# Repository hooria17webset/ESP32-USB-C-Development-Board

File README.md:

ESP32 USB-C Development Board

A compact, custom-designed ESP32 development board featuring a USB-C port for power delivery and programming. Built for makers, hobbyists, and engineers working on IoT, wireless, and embedded applications.
Features

- Microcontroller:** ESP32 (dual-core Xtensa LX6, up to 240 MHz)
- Connectivity:** Wi-Fi 802.11 b/g/n + Bluetooth 4.2 / BLE
- USB Interface:** USB-C port for power and serial programming
- Flash Memory:** 4MB (expandable depending on variant)
- GPIO: Multiple digital I/O, ADC, DAC, SPI, I2C, UART, PWM
- Power Supply:5V via USB-C or external 3.3V regulated input
- Onboard LED:Status indicator
- Reset & Boot Buttons:For easy flashing and debugging
- Compact Form Factor:Breadboard-friendly pinout

Board Pinout
Requirements

- [Arduino IDE](https://www.arduino.cc/en/software) or [PlatformIO](https://platformio.org/)
- ESP32 board support package
- USB-C cable (data-capable)
- CP2102 / CH340 driver (if needed by your OS)

Installing ESP32 Board Support (Arduino IDE)

1. Open Arduino IDE → **File > Preferences**
2. Add this URL to "Additional Board Manager URLs":
   ```
   https://raw.githubusercontent.com/espressif/arduino-esp32/gh-pages/package_esp32_index.json
   ```
3. Go to **Tools > Board > Board Manager**, search `esp32`, and install.

1. Connect the board via USB-C.
2. Select the correct **COM port** under **Tools > Port**.
3. Choose board: **ESP32 Dev Module**.
4. Upload your sketch — hold the **BOOT** button if needed during upload.

Schematic & PCB Files

> The design files are available in the `/hardware` folder.

| File | Description |
|------|-------------|
| `schematic.pdf` | Full circuit schematic |
| `pcb.kicad_pcb` | KiCad PCB layout |
| `gerbers/` | Gerber files for fabrication |
| `bom.csv` | Bill of Materials |
 Specifications

| Parameter | Value |
|-----------|-------|
| MCU | ESP32-WROOM-32 |
| CPU Speed | Up to 240 MHz |
| Flash | 4 MB |
| SRAM | 520 KB |
| Operating Voltage | 3.3V |
| Input Voltage | 5V (USB-C) |
| USB Chip | CP2102 / CH340 |
| Dimensions | ~55mm x 28mm (approx.) |
 Power

The board is powered via the **USB-C port (5V)**. An onboard **AMS1117-3.3V LDO regulator** steps down to 3.3V for the ESP32. Ensure your USB-C cable supports data transfer for programming.

## Programming Modes

| Mode | How to Enter |
|------|-------------|
| Normal Boot | Press **RESET** |
| Flash Mode | Hold **BOOT**, press **RESET**, release **BOOT** |

 Known Issues / Notes

- Some USB-C cables are charge-only — use a data-capable cable for programming.
- The onboard LDO may get warm under heavy load; keep current draw under 500mA.
- If the board isn't detected, install the appropriate USB-to-Serial driver for your OS.
 License

This project is open-source under the [MIT License](LICENSE).

## Contributing

Pull requests are welcome! If you find a bug or want to improve the design, feel free to open an issue or submit a PR.

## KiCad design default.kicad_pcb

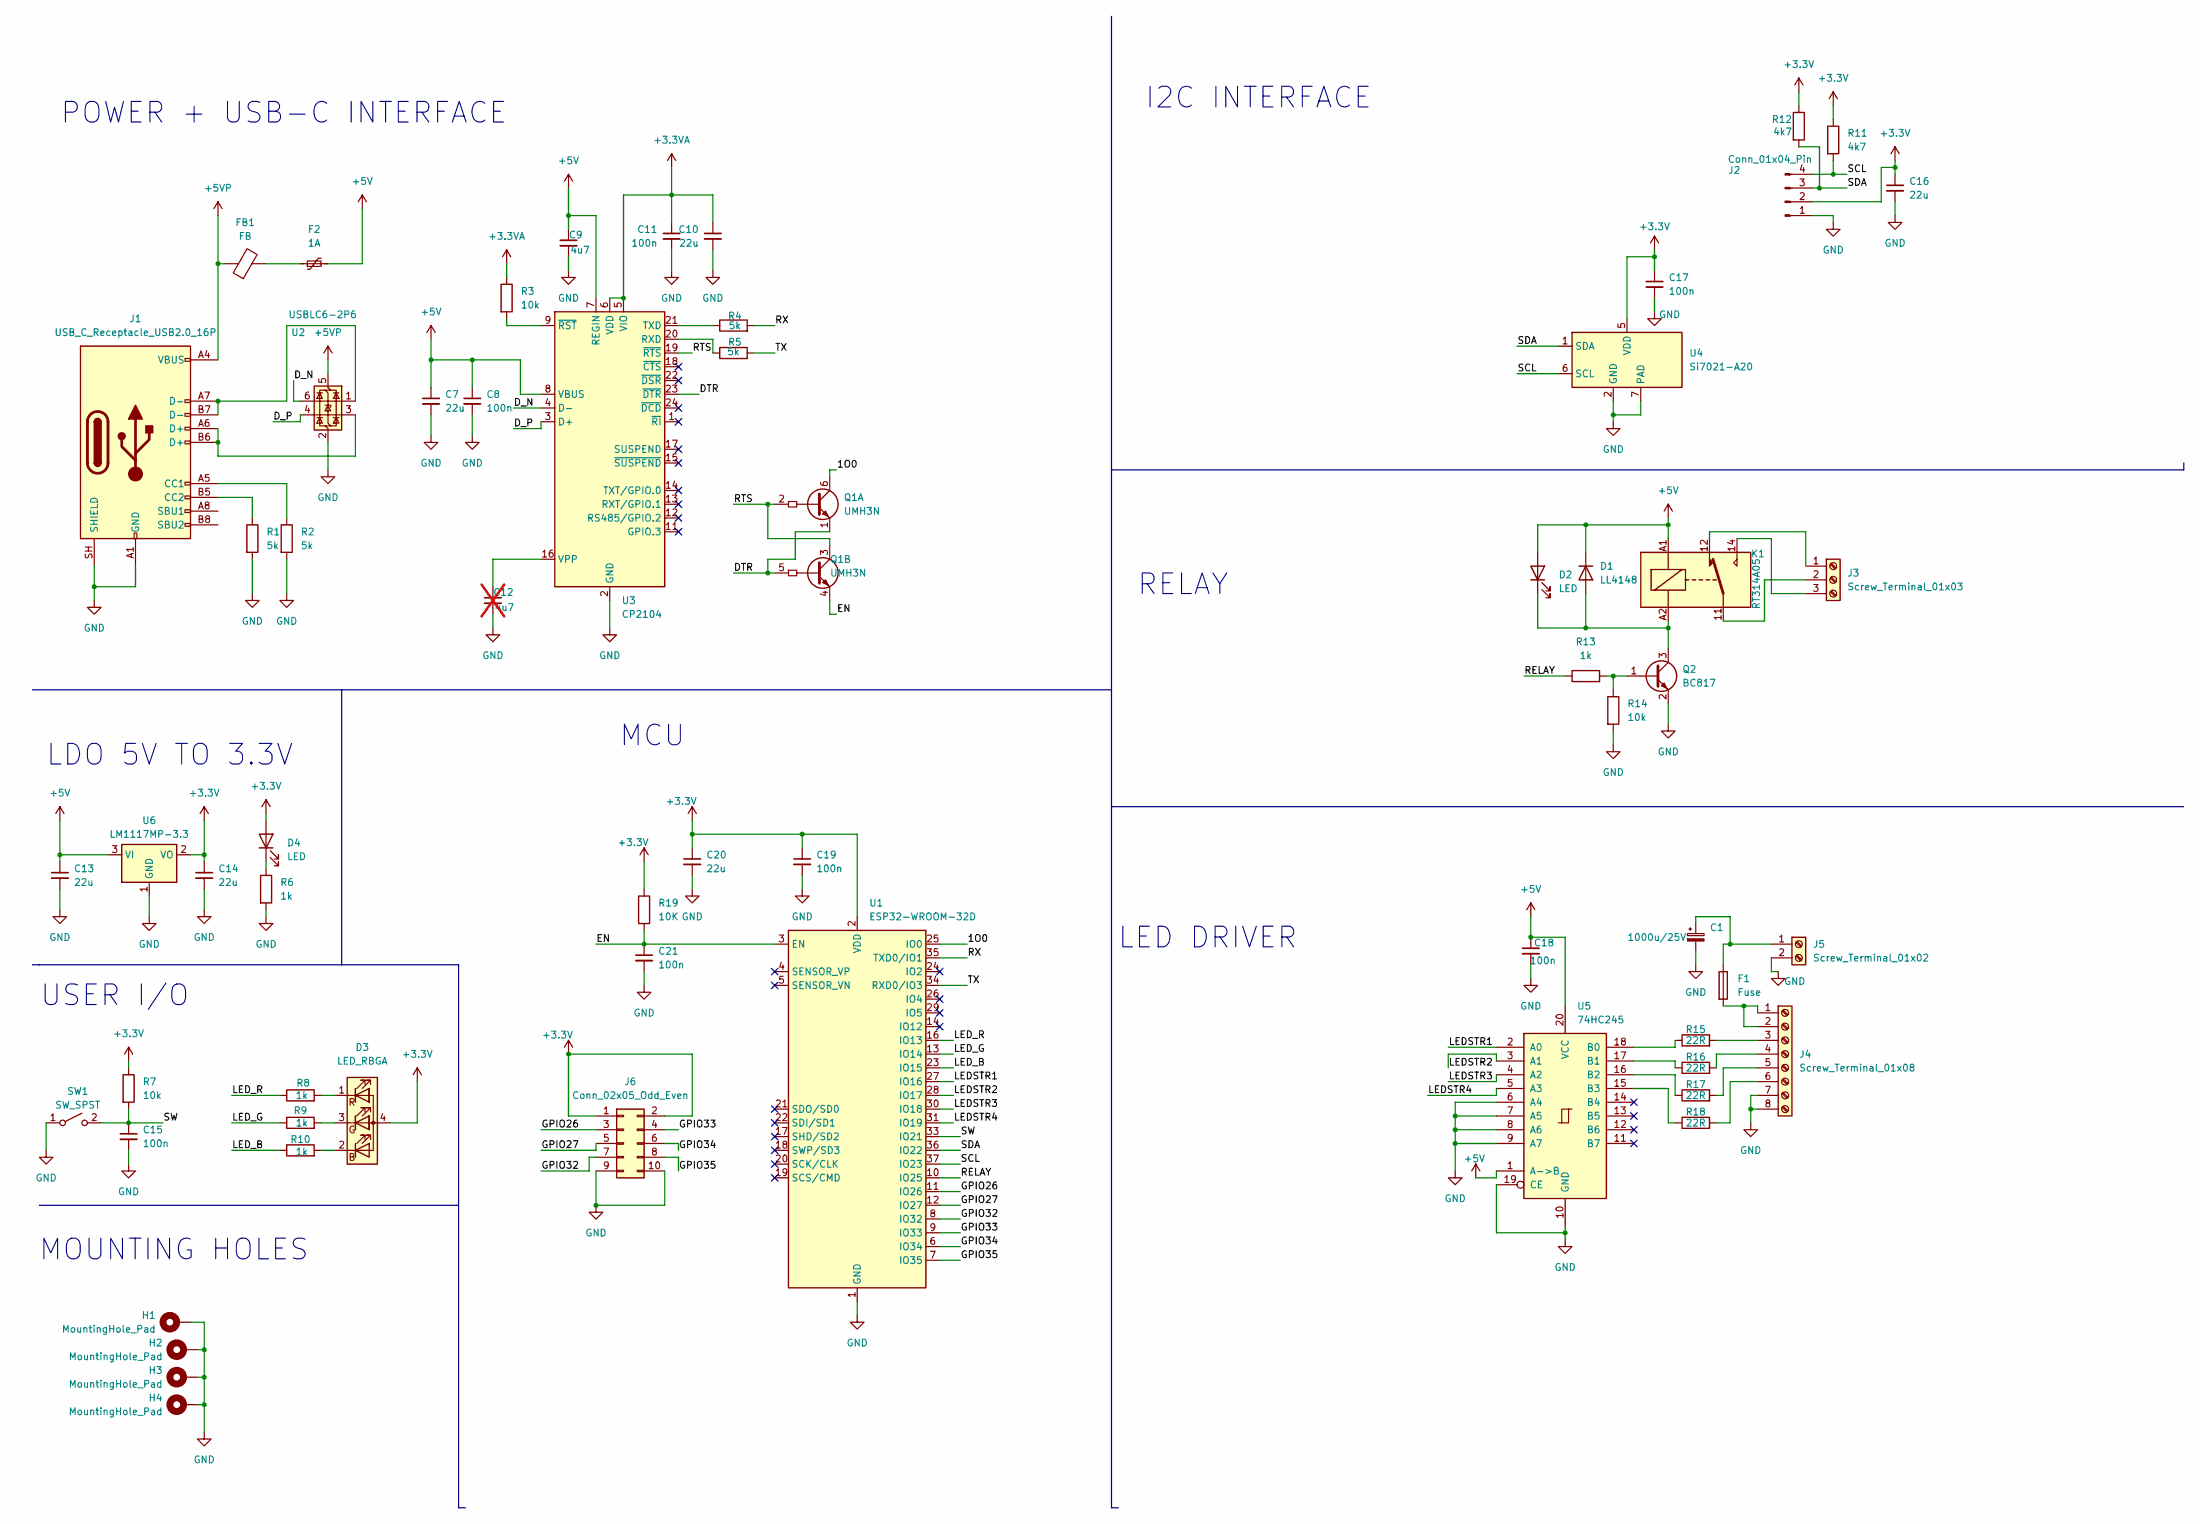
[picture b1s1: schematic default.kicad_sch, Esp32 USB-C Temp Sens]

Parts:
C1: 1000u/25V; CP_Radial_D10.0mm_P5.00mm
C7, C10, C13, C14, C16, C20: 22u; C_0805_2012Metric
C8, C11, C15, C17, C18, C19, C21: 100n; C_0402_1005Metric
C9: 4u7; C_0603_1608Metric
C12: 4u7; C_0603_1608Metric; not fitted
D1: LL4148; D_MiniMELF
D2, D4: LED; LED_0603_1608Metric
D3: LED_RBGA; LED_RGB_Wuerth-PLCC4_3.2x2.8mm_150141M173100
F1: Fuse; Fuse_1206_3216Metric
F2: 1A; Fuse_2920_7451Metric
FB1: FB; L_0603_1608Metric
H1, H2, H3, H4: MountingHole_Pad; MountingHole_3.2mm_M3_Pad_Via
J1: USB_C_Receptacle_USB2.0_16P; USB_C_Receptacle_HRO_TYPE-C-31-M-12
J2: Conn_01x04_Pin; PinHeader_1x04_P2.54mm_Horizontal
J3: Screw_Terminal_01x03; TerminalBlock_Phoenix_MKDS-1,5-3-5.08_1x03_P5.08mm_Horizont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
J4: Screw_Terminal_01x08; TerminalBlock_Phoenix_MKDS-1,5-8-5.08_1x08_P5.08mm_Horizont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
J5: Screw_Terminal_01x02; TerminalBlock_Phoenix_MKDS-1,5-2-5.08_1x02_P5.08mm_Horizont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
J6: Conn_02x05_Odd_Even; PinHeader_2x05_P2.54mm_Vertical
K1: RT314A05; Relay_SPDT_Schrack-RT1-16A-FormC_RM5mm
Q1: UMH3N; SOT-363_SC-70-6
Q2: BC817; SOT-23
R1, R2, R4, R5: 5k; R_0402_1005Metric
R3, R7, R14: 10k; R_0402_1005Metric
R6, R8, R9, R10, R13: 1k; R_0402_1005Metric
R11, R12: 4k7; R_0402_1005Metric
R15, R16, R17, R18: 22R; R_0402_1005Metric
R19: 10K; R_0402_1005Metric
SW1: SW_SPST; SW_Push_1P1T_NO_CK_PTS125Sx85PSMTR
U1: ESP32-WROOM-32D
U2: USBLC6-2P6; SOT-666
U3: CP2104; QFN-24-1EP_4x4mm_P0.5mm_EP2.6x2.6mm
U4: Si7021-A20; DFN-6-1EP_3x3mm_P1mm_EP1.5x2.4mm
U5: 74HC245; DIP-20_W7.62mm
U6: LM1117MP-3.3; SOT-223-3_TabPin2

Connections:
+3.3V: C14.1, C16.1, C17.1, C19.1, C20.1, D3.4 (A), D4.2 (A), J2.2, J6.1, J6.2, R7.1, R11.1, R12.1, R19.1, U1.2 (VDD), U4.5 (VDD), U6.2 (VO)
+3.3VA: C10.1, C11.1, R3.1, U3.5 (VIO), U3.6 (VDD)
+5V: C7.1, C8.1, C9.1, C13.1, C18.1, D1.1 (K), D2.2 (A), F2.2, K1.A1, U3.7 (REGIN), U3.8 (VBUS), U5.1 (A->B), U5.20 (VCC), U6.3 (VI)
+5VP: FB1.1, J1.A4 (VBUS), J1.A9 (VBUS), J1.B4 (VBUS), J1.B9 (VBUS), U2.5 (VBUS)
/1O0: Q1.6 (C1), U1.25 (IO0)
/DTR: Q1.1 (E1), Q1.5 (B2), U3.23 (~DTR)
/D_N: U2.6 (I/O1), U3.4 (D-)
/D_P: U2.4 (I/O2), U3.3 (D+)
/EN: C21.1, Q1.4 (E2), R19.2, U1.3 (EN)
/GPIO26: J6.3, U1.11 (IO26)
/GPIO27: J6.5, U1.12 (IO27)
/GPIO32: J6.7, U1.8 (IO32)
/GPIO33: J6.4, U1.9 (IO33)
/GPIO34: J6.6, U1.6 (IO34)
/GPIO35: J6.8, U1.7 (IO35)
/LEDSTR1: U1.27 (IO16), U5.2 (A0)
/LEDSTR2: U1.28 (IO17), U5.3 (A1)
/LEDSTR3: U1.30 (IO18), U5.4 (A2)
/LEDSTR4: U1.31 (IO19), U5.5 (A3)
/LED_B: R10.1, U1.23 (IO15)
/LED_G: R9.1, U1.13 (IO14)
/LED_R: R8.1, U1.16 (IO13)
/RELAY: R13.1, U1.10 (IO25)
/RTS: Q1.2 (B1), Q1.3 (C2), U3.19 (~RTS)
/RX: R4.2, U1.35 (TXD0/IO1)
/SCL: J2.4, R11.2, U1.37 (IO23), U4.6 (SCL)
/SDA: J2.3, R12.2, U1.36 (IO22), U4.1 (SDA)
/SW: C15.1, R7.2, SW1.2 (B), U1.33 (IO21)
/TX: R5.2, U1.34 (RXD0/IO3)
GND: C1.2, C7.2, C8.2, C9.2, C10.2, C11.2, C12.2, C13.2, C14.2, C15.2, C16.2, C17.2, C18.2, C19.2, C20.2, C21.2, H1.1 (1_1), H2.1 (1_1), H3.1 (1_1), H4.1 (1_1), J1.A1 (GND), J1.A12 (GND), J1.B1 (GND), J1.B12 (GND), J1.SH (SHIELD), J2.1, J4.7, J4.8, J5.2, J6.9, J6.10, Q2.2 (E), R1.2, R2.2, R6.2, R14.2, SW1.1 (A), U1.1 (GND), U1.15 (GND), U1.38 (GND), U1.39 (GND), U2.2 (GND), U3.2 (GND), U3.25 (GND), U4.2 (GND), U4.7 (PAD), U5.6 (A4), U5.7 (A5), U5.8 (A6), U5.9 (A7), U5.10 (GND), U5.19 (CE), U6.1 (GND)
unnamed: D1.2 (A), D2.1 (K), K1.A2, Q2.3 (C)
unnamed: D3.2 (BK), R10.2
unnamed: D3.3 (GK), R9.2
unnamed: D3.1 (RK), R8.2
unnamed: D4.1 (K), R6.1
unnamed: F2.1, FB1.2
unnamed: J1.A5 (CC1), R2.1
unnamed: J1.B5 (CC2), R1.1
unnamed: J1.A6 (D+), J1.B6 (D+), U2.3 (I/O2)
unnamed: J1.A7 (D-), J1.B7 (D-), U2.1 (I/O1)
unnamed: J3.1, K1.12
unnamed: J3.2, K1.11
unnamed: J3.3, K1.14
unnamed: F1.2, J4.1, J4.2
unnamed: J4.3, R15.2
unnamed: J4.4, R16.2
unnamed: J4.5, R17.2
unnamed: J4.6, R18.2
unnamed: C1.1, F1.1, J5.1
unnamed: Q2.1 (B), R13.2, R14.1
unnamed: R5.1, U3.20 (RXD)
unnamed: R4.1, U3.21 (TXD)
unnamed: C12.1, U3.16 (VPP)
unnamed: R3.2, U3.9 (~RST)
unnamed: R15.1, U5.18 (B0)
unnamed: R16.1, U5.17 (B1)
unnamed: R17.1, U5.16 (B2)
unnamed: R18.1, U5.15 (B3)

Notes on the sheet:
LDO 5V TO 3.3V
USER I/O
RELAY
MOUNTING HOLES
LED DRIVER
I2C INTERFACE
POWER + USB-C INTERFACE
MCU

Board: 4 copper layers, 62 parts (0 on the bottom side), 58 nets, no tracks yet.
